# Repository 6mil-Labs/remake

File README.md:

# REMAKE

REMAKE is a **36-key wireless split keyboard** designed by **Felipe Balbi**
around RMK firmware. Its name includes **RMK**.

Each half has 15 finger keys and a three-key thumb cluster. The stepped board
outline follows the column stagger and thumb fan. Both halves use the same
reversible PCB: manufacture **two separate, identical boards** and populate
them in opposite orientations. No panelization or mouse bites are required.

## Revision validation status

| Revision | Status |
|---|---|
| REV 0.1 | Fully validated |
| REV 0.2 | Fully validated |
| [REV 0.3](https://github.com/6mil-Labs/remake/releases/tag/v0.3) | Current prerelease; physical validation remains required |

> **REV 0.3 is prototype hardware, not production-fit or safety certification.** The current design has
> **18 keys per half / 36 total.** Routing is complete, ground pours are filled,
> and the outline is closed with straight runs and circular fillets, with at least
> **3.5 mm nominal switch-body margin** around the key matrix. SW17's
> larger PCB envelope contains a **26.5×16.5 mm cap**, rotated
> 90° relative to its original thumb fan; other caps use **17.5×16.5 mm** envelopes.
> The minimum nominal thumb-to-row gap is approximately **0.660 mm**.
> Production tolerances and moving-key fit have not been physically validated.
> Component selection and physical validation are incomplete. The battery
> receptacles moved **4 mm upward** to improve lead reach. **PCB v0.3 uses
> Case v1.0**, not Case v0.2. Firmware is maintained and tested separately.

## v0.3 release and editable sources

- [Published v0.3 prerelease](https://github.com/6mil-Labs/remake/releases/tag/v0.3):
  fabrication ZIP, schematic PDF, assembly PNG/STEP previews, Case v1.0 left/right
  STEP bodies, model-coverage notes, and `SHA256SUMS`.
- [Tagged v0.3 sources](https://github.com/6mil-Labs/remake/tree/v0.3): editable
  KiCad project/schematic/PCB and FreeCAD case sources. GitHub's source archives
  on the release page contain these files; Gerbers and STEP exports are not a
  replacement for the editable sources.

Use two identical PCBs per keyboard. Keep assembly models (`remake-*.step`)
separate from case bodies (`case-v1.0-*.step`), and review model omissions and
physical-fit requirements before fabrication or assembly.

## Repository layout

| Path | Contents |
|---|---|
| [`hw/`](hw/) | KiCad project, schematic, PCB, local libraries and library tables |
| [`cad/`](cad/) | Component models, source manifest and third-party notices |
| [`docs/`](docs/) | Assembly, manufacturing and component references |
| [`docs/assets/`](docs/assets/) | Vector logo and source artwork |
| [`.github/workflows/`](.github/workflows/) | KiCad checks; no automatic source commits |

The root contains project-level documentation and licensing. Generated reports
and exports belong in ignored output directories, not alongside source files.

## Open the hardware

Use **KiCad 10.0.7 or newer** and open [`hw/remake.kicad_pro`](hw/remake.kicad_pro).
Local library tables and project-relative model paths travel with the project.

On this machine, use the following workaround for the native Wayland issue:

```sh
GDK_BACKEND=x11 kicad hw/remake.kicad_pro
```

Read [assembly](docs/assembly.md) before building. The
[component reference](docs/components.md) records sources, licences and model
limitations; a rendering is not proof of fit. The regression suite checks
schematic-to-PCB associations separately from electrical parity.

## Firmware

[REMAKE Miryoku](https://github.com/6mil-Labs/remake-miryoku) contains the
RMK-based firmware, complete keyboard configuration, build/flash instructions,
and native tests. It provides left/central and right/peripheral UF2 images;
flash matching builds to both nice!nano v2 controllers. Firmware is versioned
separately from the PCB: use its documented REMAKE pin mapping and check the
actual assembly. Hardware CI does not build or certify the firmware.

## Checks

Run from the repository root, with reports outside the source tree:

```sh
mkdir -p .remake-checks
kicad-cli pcb drc --format json --refill-zones --schematic-parity \
  --output .remake-checks/drc.json hw/remake.kicad_pcb
kicad-cli sch erc --format json \
  --output .remake-checks/erc.json hw/remake.kicad_sch
```

Before fabrication, require clean refilled DRC, zero unconnected items and
schematic parity, and review all ERC findings. Use `--exit-code-violations` for
gated checks. Do not hide findings, weaken rules or bridge selection jumpers
to make checks pass. Component-rating, physical assembly, battery-safety and
prototype/RF checks remain required even when CAD checks pass.

Run the regression suite as well:

```sh
python3 -m unittest discover -s tests -v
```

## Draft releases

Pushing a tag runs the same required CI on that exact commit. Only after CI
and fabrication packaging succeed does the workflow create a **draft** GitHub
Release containing one-design JLCPCB fabrication ZIP, a schematic PDF,
left/right PNG and STEP previews, compatible Case v1.0 body STEP files,
model-coverage notes and checksums. These files are separate attachments, never
additional designs inside the JLCPCB ZIP. The STEP assemblies are partial;
check their coverage notes before case design. Branch/PR CI also exports the
case solids for both case versions as the `case-steps` artifact, including on
case-only changes. PCB v0.3 uses Case v1.0; case and PCB revision numbers differ.
Review and publish the draft manually; failed, cancelled or skipped prerequisites
block release creation. Passing CI is not physical/fabrication approval.

See [manufacturing and release details](docs/manufacturing.md) for archive
contents, validation limits and retry behavior.

## OSHWA certification

REMAKE is **not yet OSHWA-certified**. Open-source licensing, passing CI, and
the generic open-hardware gear logo are not the OSHWA certification mark.

The [submission guide](docs/oshwa.md) documents the standard-library Python
helper, API-token signup, and editable application template. Preview is offline
by default; submitting requires explicit legal declarations and `--submit`.
Point an application at the public source/release version being certified, not
an unpublished future v1.0. Wait for OSHWA approval and a UID before using the
certification mark on a PCB.

## Contributing and licensing

See [CONTRIBUTING.md](CONTRIBUTING.md) for source organization and validation
expectations.

**Copyright © 2026 Felipe Balbi.** REMAKE is licensed under the
**CERN Open Hardware Licence Version 2 — Strongly Reciprocal**
([CERN-OHL-S-2.0](LICENSE)); see [COPYRIGHT](COPYRIGHT) for the project notice.
Project-authored written documentation and original documentation illustrations
are additionally available under [CC-BY-SA-4.0](LICENSE-DOCUMENTATION.md), at
your option. Hardware/design files retain their existing licence.
Imported third-party component models and library sources retain their
documented licences and notices. Local-only models with unresolved
redistribution rights are not covered by the project licence grant.

### Manufacturing and sales

Interested in manufacturing or selling REMAKE boards or kits? I'd love to hear
from you! Please [open a manufacturing and sales issue](https://github.com/6mil-Labs/remake/issues/new?template=manufacturing-and-sales.yml)
to discuss revisions, manufacturing feedback, and opportunities to collaborate.
You can also opt in to a future seller list to help people find bare PCBs, kits,
or assembled keyboards without building everything themselves.

Commercial manufacture and sale are permitted under [CERN-OHL-S-2.0](LICENSE),
subject to its requirements. Contacting the maintainer is encouraged, but is not
a condition of exercising those rights. Third-party products must not be
presented as officially endorsed without permission.

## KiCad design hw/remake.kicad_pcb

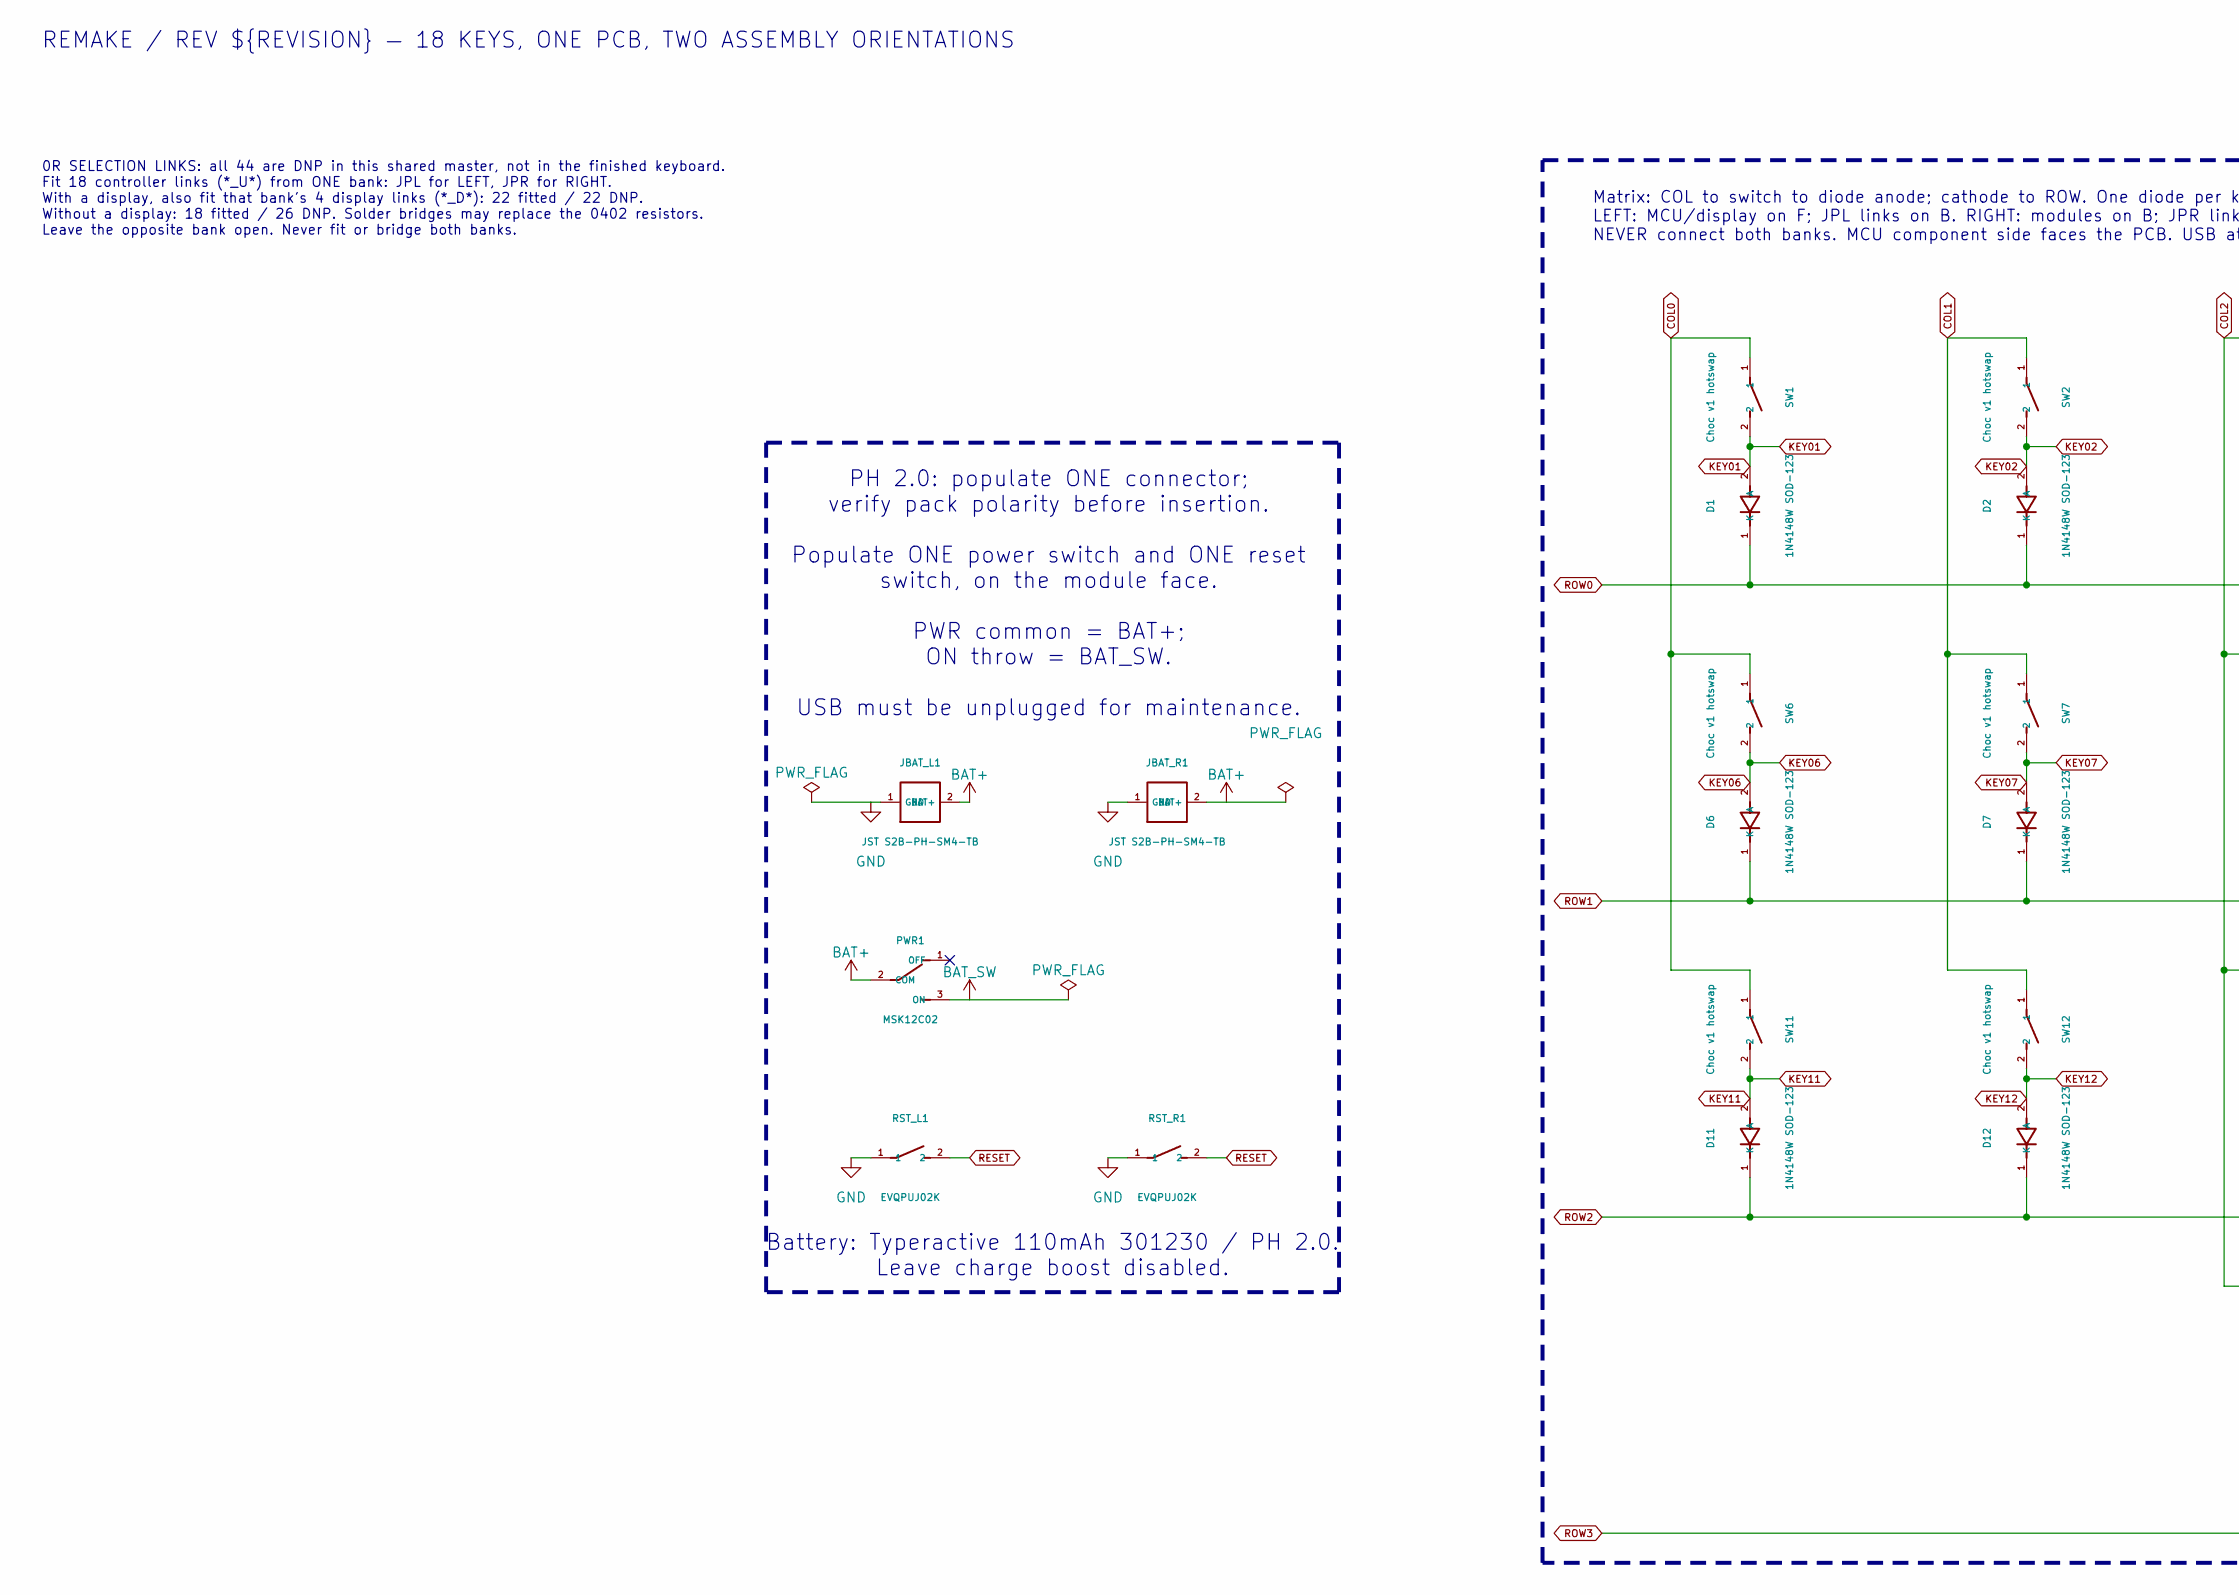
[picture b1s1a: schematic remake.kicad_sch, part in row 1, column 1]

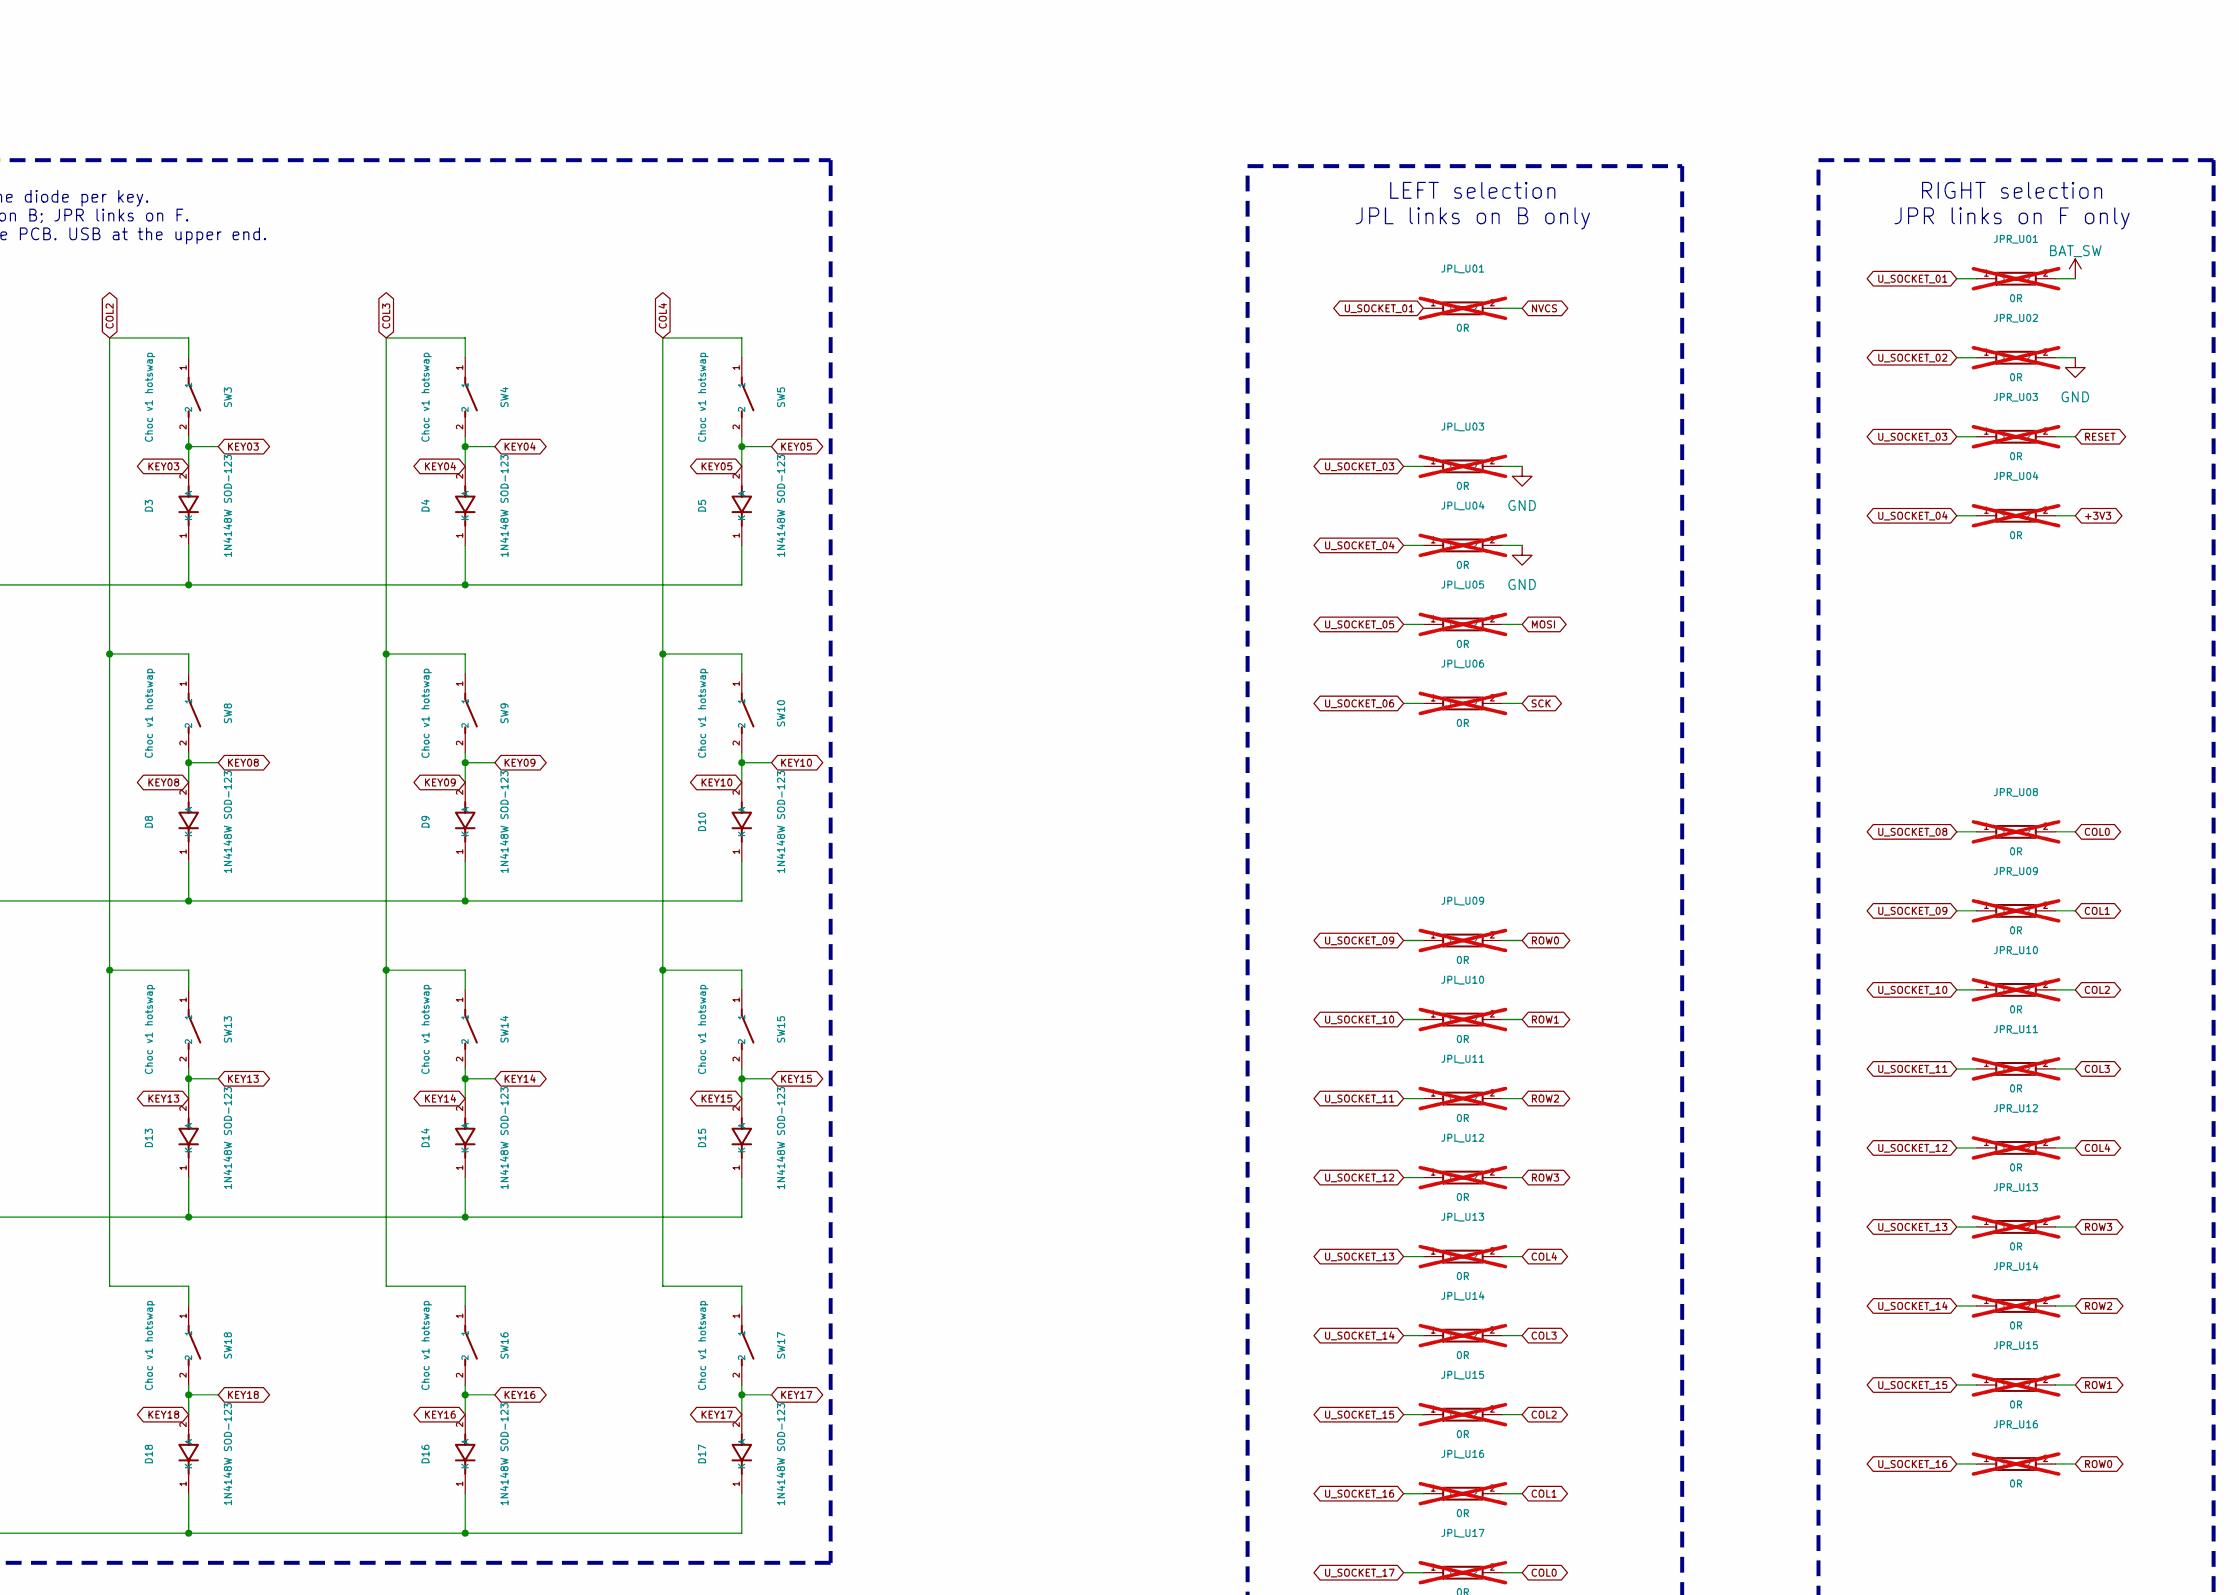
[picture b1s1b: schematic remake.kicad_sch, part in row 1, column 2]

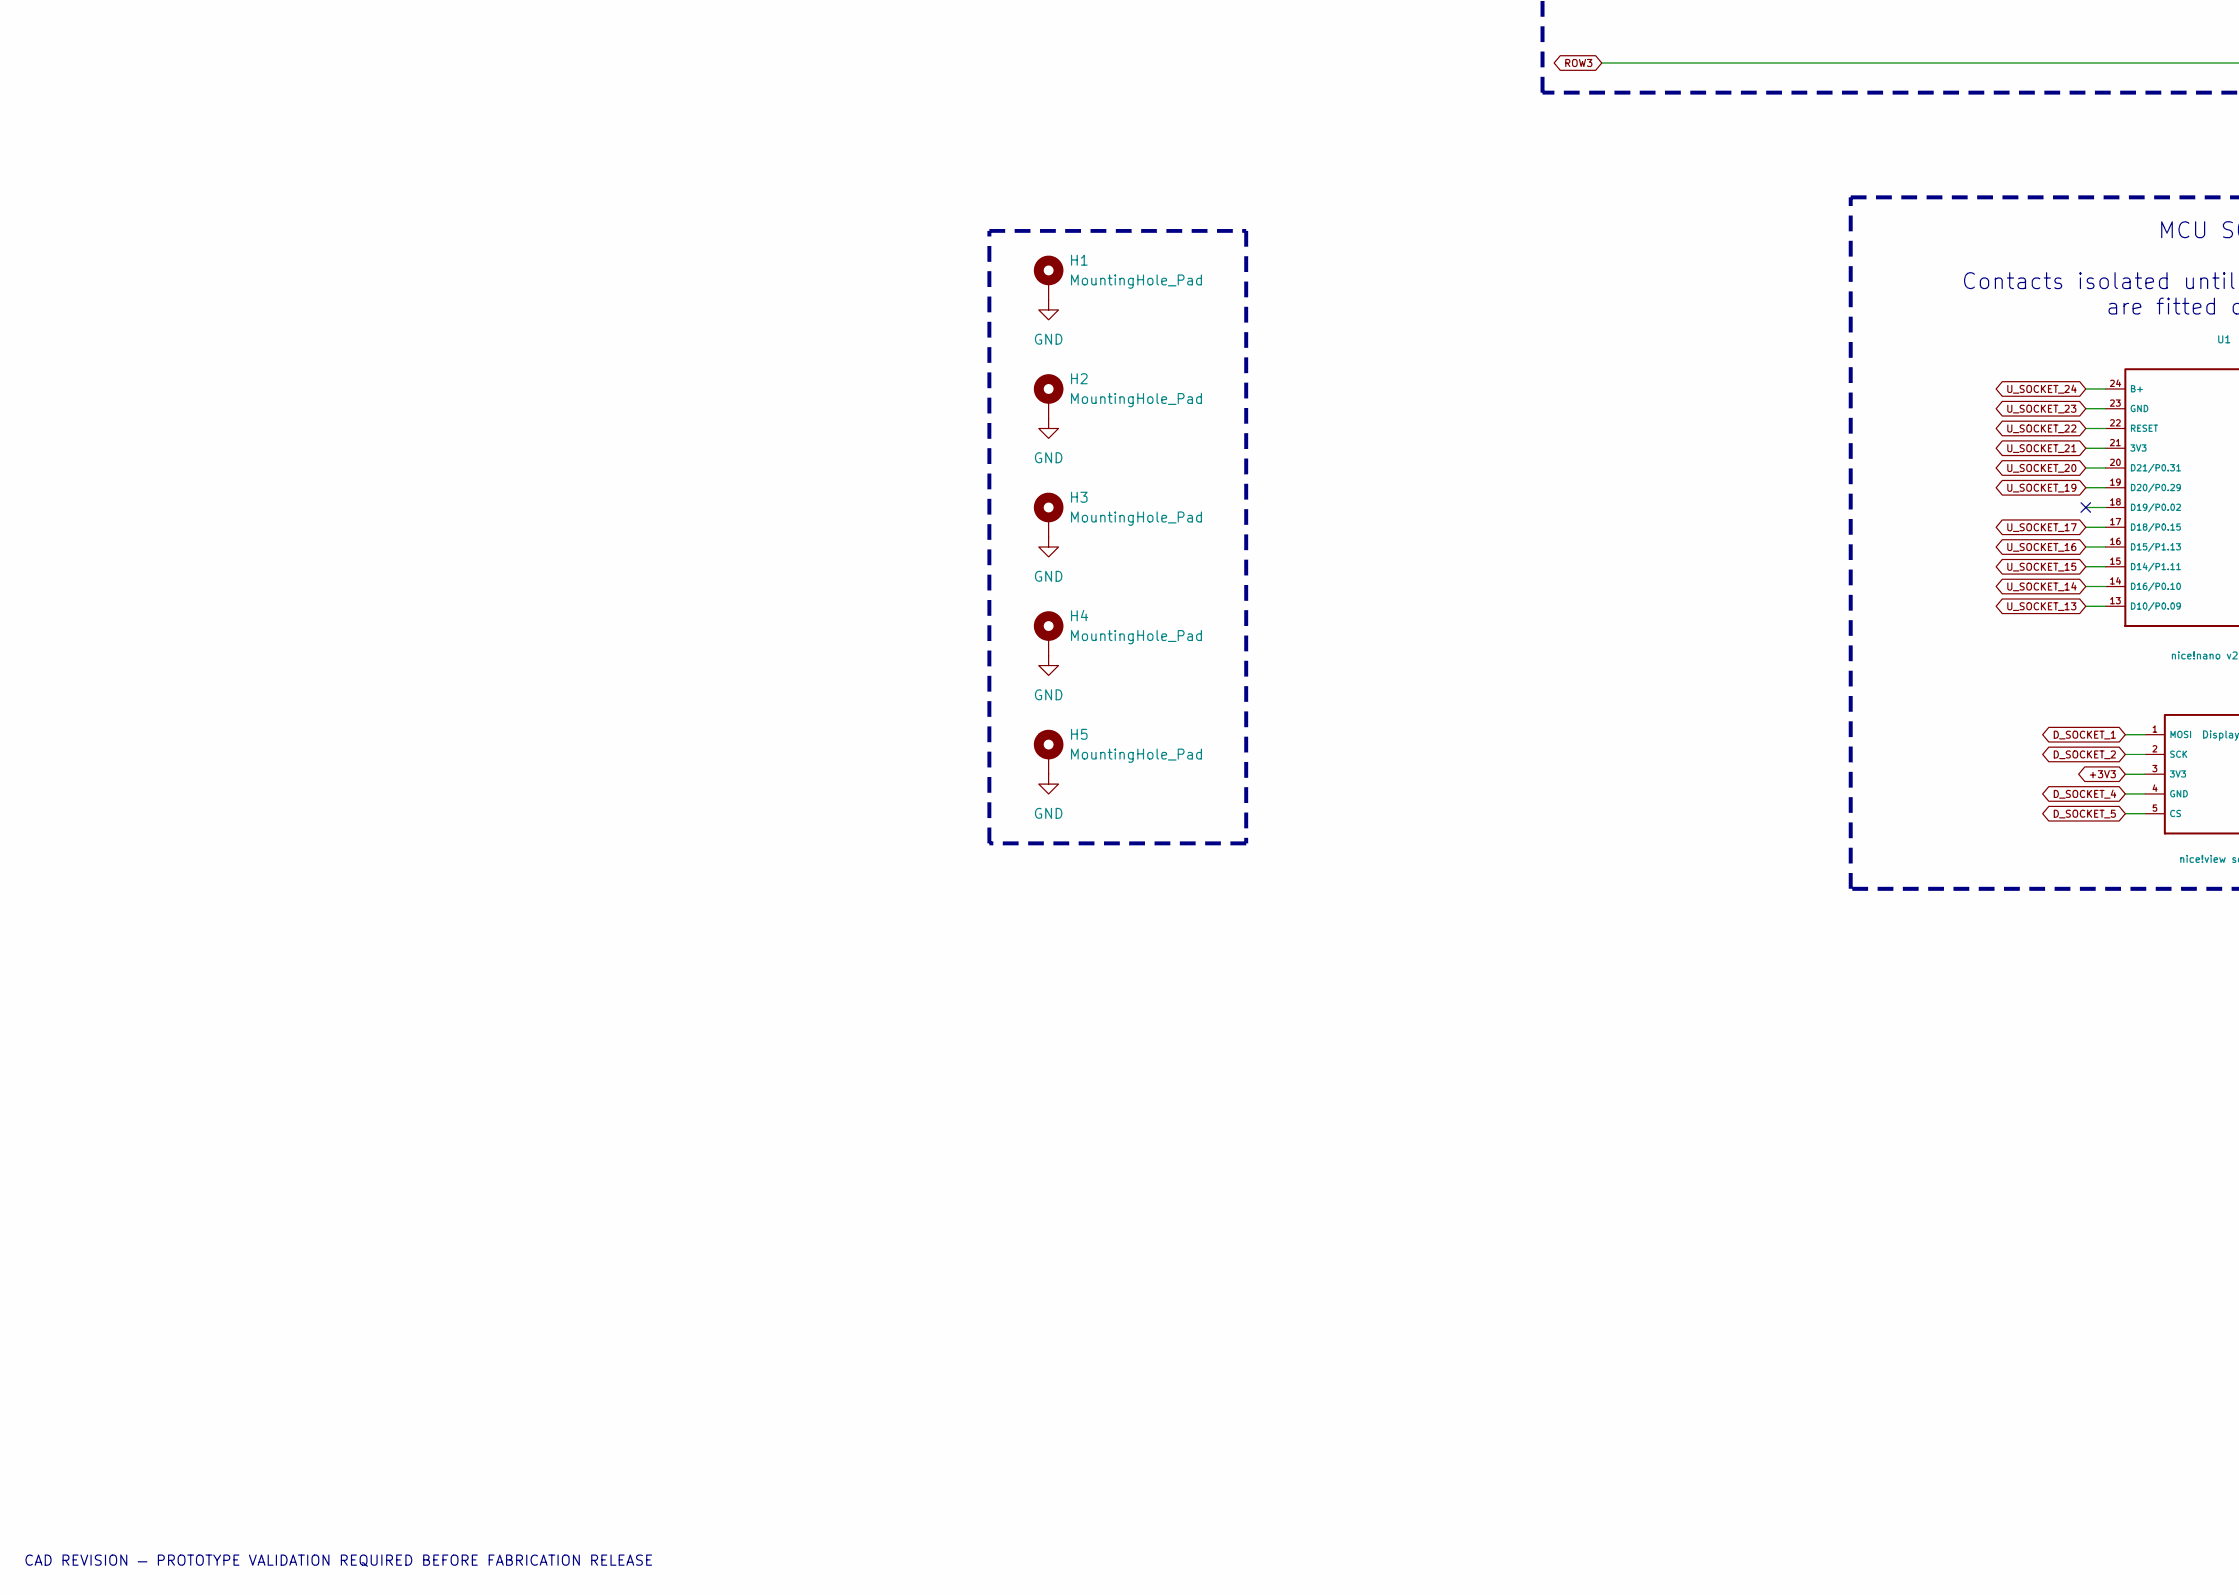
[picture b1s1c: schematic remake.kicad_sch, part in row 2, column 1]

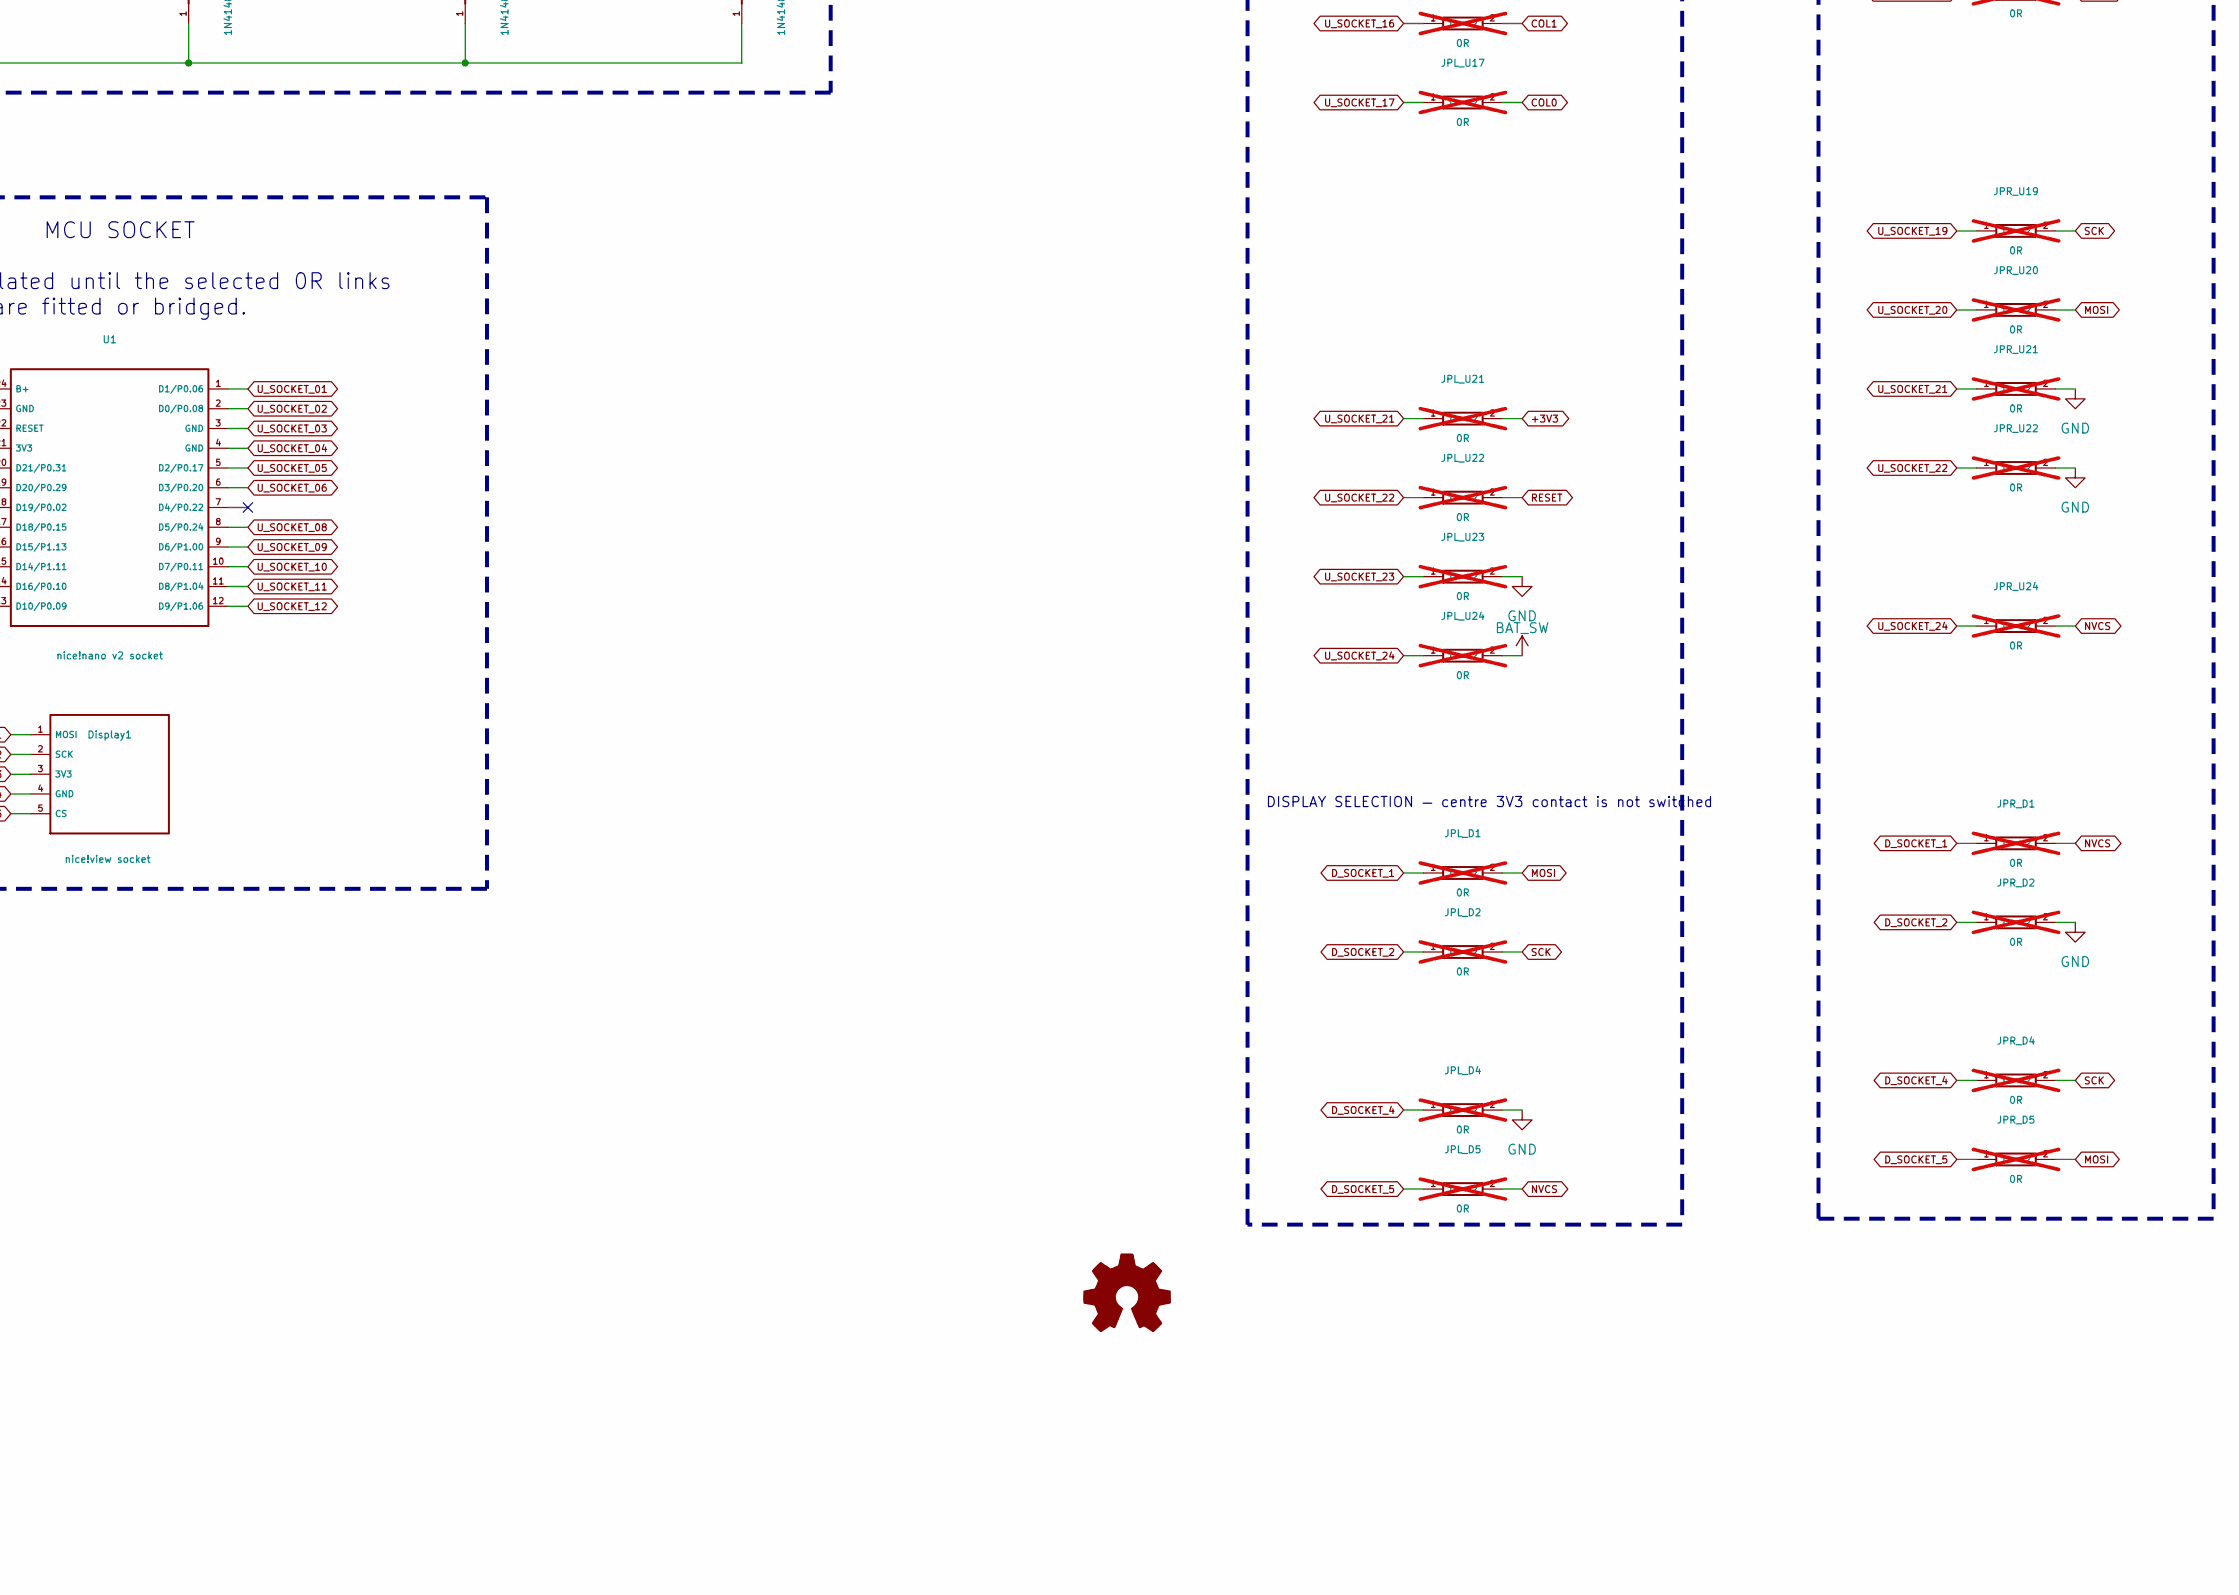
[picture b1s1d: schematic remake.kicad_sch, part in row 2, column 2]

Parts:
D1, D2, D3, D4, D5, D6, D7, D8, D9, D10, D11, D12, D13, D14, D15, D16, D17, D18: 1N4148W SOD-123; Diode_SOD123_reversible
Display1: nice!view socket; nice_view_reversible
H1, H2, H3, H4, H5: MountingHole_Pad; MountingHole_2.2mm_M2_ISO7380_Pad_TopBottom
JBAT_L1: JST S2B-PH-SM4-TB; JST_PH_2mm_side_entry
JBAT_R1: JST S2B-PH-SM4-TB; JST_PH_2mm_side_entry
JPL_D1, JPL_D2, JPL_D4, JPL_D5: 0R; R_0402_1005Metric_SolderJumper; not fitted
JPL_U01, JPL_U03, JPL_U04, JPL_U05, JPL_U06, JPL_U09, JPL_U10, JPL_U11, JPL_U12, JPL_U13, JPL_U14, JPL_U15, JPL_U16, JPL_U17, JPL_U21, JPL_U22, JPL_U23, JPL_U24: 0R; R_0402_1005Metric_SolderJumper; not fitted
JPR_D1, JPR_D2, JPR_D4, JPR_D5: 0R; R_0402_1005Metric_SolderJumper; not fitted
JPR_U01, JPR_U02, JPR_U03, JPR_U04, JPR_U08, JPR_U09, JPR_U10, JPR_U11, JPR_U12, JPR_U13, JPR_U14, JPR_U15, JPR_U16, JPR_U19, JPR_U20, JPR_U21, JPR_U22, JPR_U24: 0R; R_0402_1005Metric_SolderJumper; not fitted
PWR1: MSK12C02; SW_Power_MSK12C02_reversible
RST_L1: EVQPUJ02K; SW_SPST_Panasonic_EVQPUJ02K
RST_R1: EVQPUJ02K; SW_SPST_Panasonic_EVQPUJ02K
SW1, SW2, SW3, SW4, SW5, SW6, SW7, SW8, SW9, SW10, SW11, SW12, SW13, SW14, SW15, SW16, SW17, SW18: Choc v1 hotswap; SW_Hotswap_Kailh_Choc_V1_reversible
U1: nice!nano v2 socket; nice_nano_reversible

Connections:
+3V3: Display1.3 (3V3), JPL_U21.2, JPR_U04.2
BAT+: JBAT_L1.2 (BAT+), JBAT_R1.2 (BAT+), PWR1.2 (COM)
BAT_SW: JPL_U24.2, JPR_U01.2, PWR1.3 (ON)
COL0: JPL_U17.2, JPR_U08.2, SW1.1, SW6.1, SW11.1
COL1: JPL_U16.2, JPR_U09.2, SW2.1, SW7.1, SW12.1
COL2: JPL_U15.2, JPR_U10.2, SW3.1, SW8.1, SW13.1, SW18.1
COL3: JPL_U14.2, JPR_U11.2, SW4.1, SW9.1, SW14.1, SW16.1
COL4: JPL_U13.2, JPR_U12.2, SW5.1, SW10.1, SW15.1, SW17.1
D_SOCKET_1: Display1.1 (MOSI), JPL_D1.1, JPR_D1.1
D_SOCKET_2: Display1.2 (SCK), JPL_D2.1, JPR_D2.1
D_SOCKET_4: Display1.4 (GND), JPL_D4.1, JPR_D4.1
D_SOCKET_5: Display1.5 (CS), JPL_D5.1, JPR_D5.1
GND: H1.1 (1_1), H2.1 (1_1), H3.1 (1_1), H4.1 (1_1), H5.1 (1_1), JBAT_L1.1 (GND), JBAT_R1.1 (GND), JPL_D4.2, JPL_U03.2, JPL_U04.2, JPL_U23.2, JPR_D2.2, JPR_U02.2, JPR_U21.2, JPR_U22.2, RST_L1.1, RST_R1.1
KEY01: D1.2 (A), SW1.2
KEY02: D2.2 (A), SW2.2
KEY03: D3.2 (A), SW3.2
KEY04: D4.2 (A), SW4.2
KEY05: D5.2 (A), SW5.2
KEY06: D6.2 (A), SW6.2
KEY07: D7.2 (A), SW7.2
KEY08: D8.2 (A), SW8.2
KEY09: D9.2 (A), SW9.2
KEY10: D10.2 (A), SW10.2
KEY11: D11.2 (A), SW11.2
KEY12: D12.2 (A), SW12.2
KEY13: D13.2 (A), SW13.2
KEY14: D14.2 (A), SW14.2
KEY15: D15.2 (A), SW15.2
KEY16: D16.2 (A), SW16.2
KEY17: D17.2 (A), SW17.2
KEY18: D18.2 (A), SW18.2
MOSI: JPL_D1.2, JPL_U05.2, JPR_D5.2, JPR_U20.2
NVCS: JPL_D5.2, JPL_U01.2, JPR_D1.2, JPR_U24.2
RESET: JPL_U22.2, JPR_U03.2, RST_L1.2, RST_R1.2
ROW0: D1.1 (K), D2.1 (K), D3.1 (K), D4.1 (K), D5.1 (K), JPL_U09.2, JPR_U16.2
ROW1: D6.1 (K), D7.1 (K), D8.1 (K), D9.1 (K), D10.1 (K), JPL_U10.2, JPR_U15.2
ROW2: D11.1 (K), D12.1 (K), D13.1 (K), D14.1 (K), D15.1 (K), JPL_U11.2, JPR_U14.2
ROW3: D16.1 (K), D17.1 (K), D18.1 (K), JPL_U12.2, JPR_U13.2
SCK: JPL_D2.2, JPL_U06.2, JPR_D4.2, JPR_U19.2
U_SOCKET_01: JPL_U01.1, JPR_U01.1, U1.1 (D1/P0.06)
U_SOCKET_02: JPR_U02.1, U1.2 (D0/P0.08)
U_SOCKET_03: JPL_U03.1, JPR_U03.1, U1.3 (GND)
U_SOCKET_04: JPL_U04.1, JPR_U04.1, U1.4 (GND)
U_SOCKET_05: JPL_U05.1, U1.5 (D2/P0.17)
U_SOCKET_06: JPL_U06.1, U1.6 (D3/P0.20)
U_SOCKET_08: JPR_U08.1, U1.8 (D5/P0.24)
U_SOCKET_09: JPL_U09.1, JPR_U09.1, U1.9 (D6/P1.00)
U_SOCKET_10: JPL_U10.1, JPR_U10.1, U1.10 (D7/P0.11)
U_SOCKET_11: JPL_U11.1, JPR_U11.1, U1.11 (D8/P1.04)
U_SOCKET_12: JPL_U12.1, JPR_U12.1, U1.12 (D9/P1.06)
U_SOCKET_13: JPL_U13.1, JPR_U13.1, U1.13 (D10/P0.09)
U_SOCKET_14: JPL_U14.1, JPR_U14.1, U1.14 (D16/P0.10)
U_SOCKET_15: JPL_U15.1, JPR_U15.1, U1.15 (D14/P1.11)
U_SOCKET_16: JPL_U16.1, JPR_U16.1, U1.16 (D15/P1.13)
U_SOCKET_17: JPL_U17.1, U1.17 (D18/P0.15)
U_SOCKET_19: JPR_U19.1, U1.19 (D20/P0.29)
U_SOCKET_20: JPR_U20.1, U1.20 (D21/P0.31)
U_SOCKET_21: JPL_U21.1, JPR_U21.1, U1.21 (3V3)
U_SOCKET_22: JPL_U22.1, JPR_U22.1, U1.22 (RESET)
U_SOCKET_23: JPL_U23.1, U1.23 (GND)
U_SOCKET_24: JPL_U24.1, JPR_U24.1, U1.24 (B+)

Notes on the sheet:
DISPLAY SELECTION — centre 3V3 contact is not switched
CAD REVISION — PROTOTYPE VALIDATION REQUIRED BEFORE FABRICATION RELEASE
REMAKE / REV ${REVISION} — 18 KEYS, ONE PCB, TWO ASSEMBLY ORIENTATIONS
LEFT selection JPL links on B only
PH 2.0: populate ONE connector; verify pack polarity before insertion. Populate ONE power switch and ONE reset switch, on the module face. PWR common = BAT+; ON throw = BAT_SW. USB must be unplugged for maintenance.
MCU SOCKET Contacts isolated until the selected 0R links are fitted or bridged.
Matrix: COL to switch to diode anode; cathode to ROW. One diode per key. LEFT: MCU/display on F; JPL links on B. RIGHT: modules on B; JPR links on F. NEVER connect both banks. MCU component side faces the PCB. USB at the upper end.
Battery: Typeractive 110mAh 301230 / PH 2.0. Leave charge boost disabled.
RIGHT selection JPR links on F only
0R SELECTION LINKS: all 44 are DNP in this shared master, not in the finished keyboard. Fit 18 controller links (*_U*) from ONE bank: JPL for LEFT, JPR for RIGHT. With a display, also fit that bank's 4 display links (*_D*): 22 fitted / 22 DNP. Without a display: 18 fitted / 26 DNP. Solder bridges m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

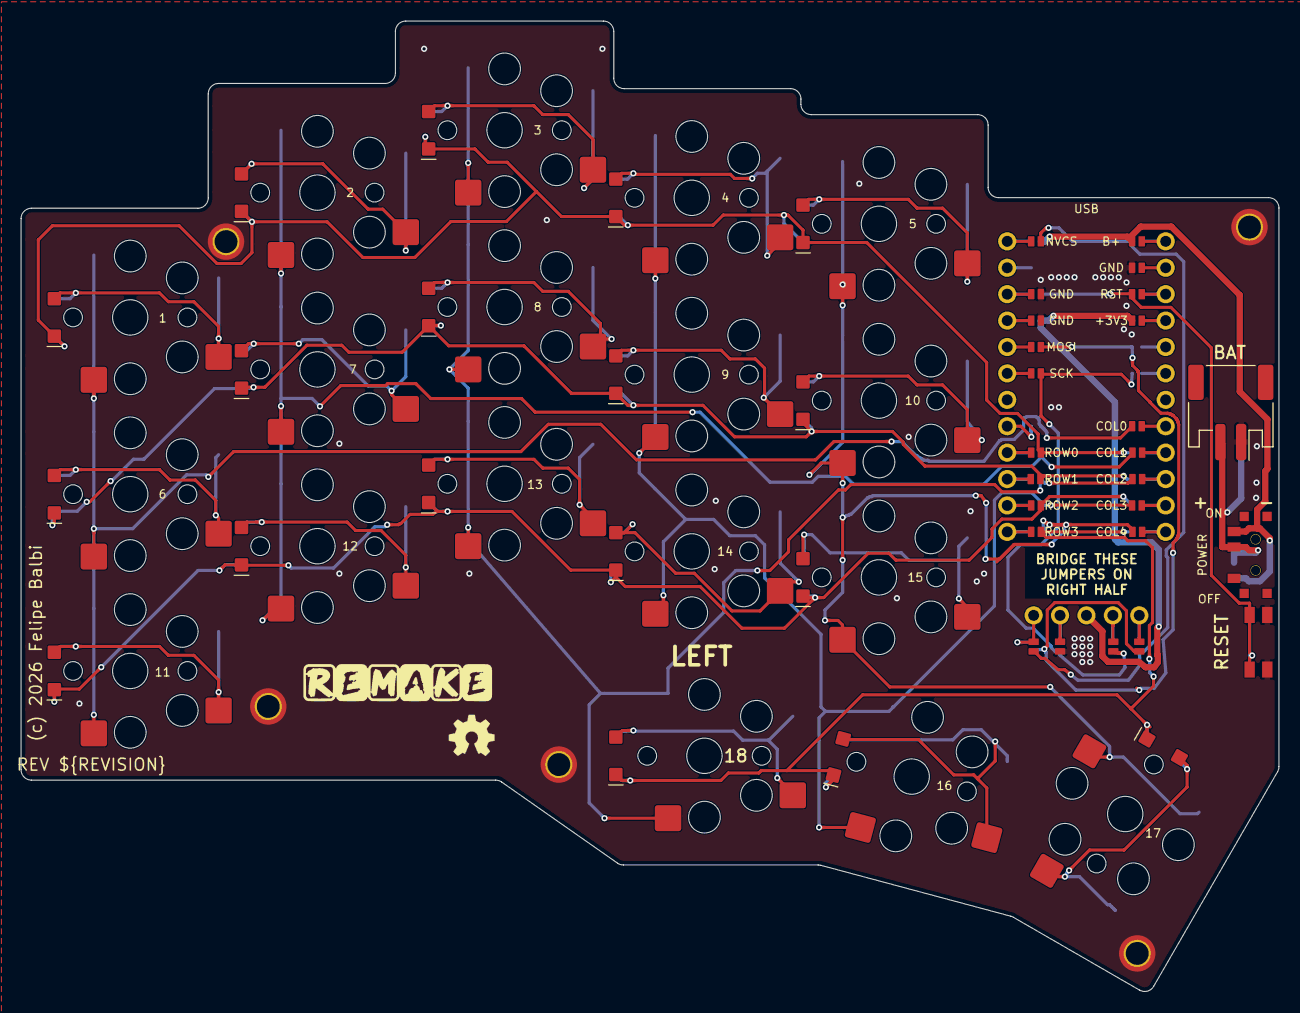
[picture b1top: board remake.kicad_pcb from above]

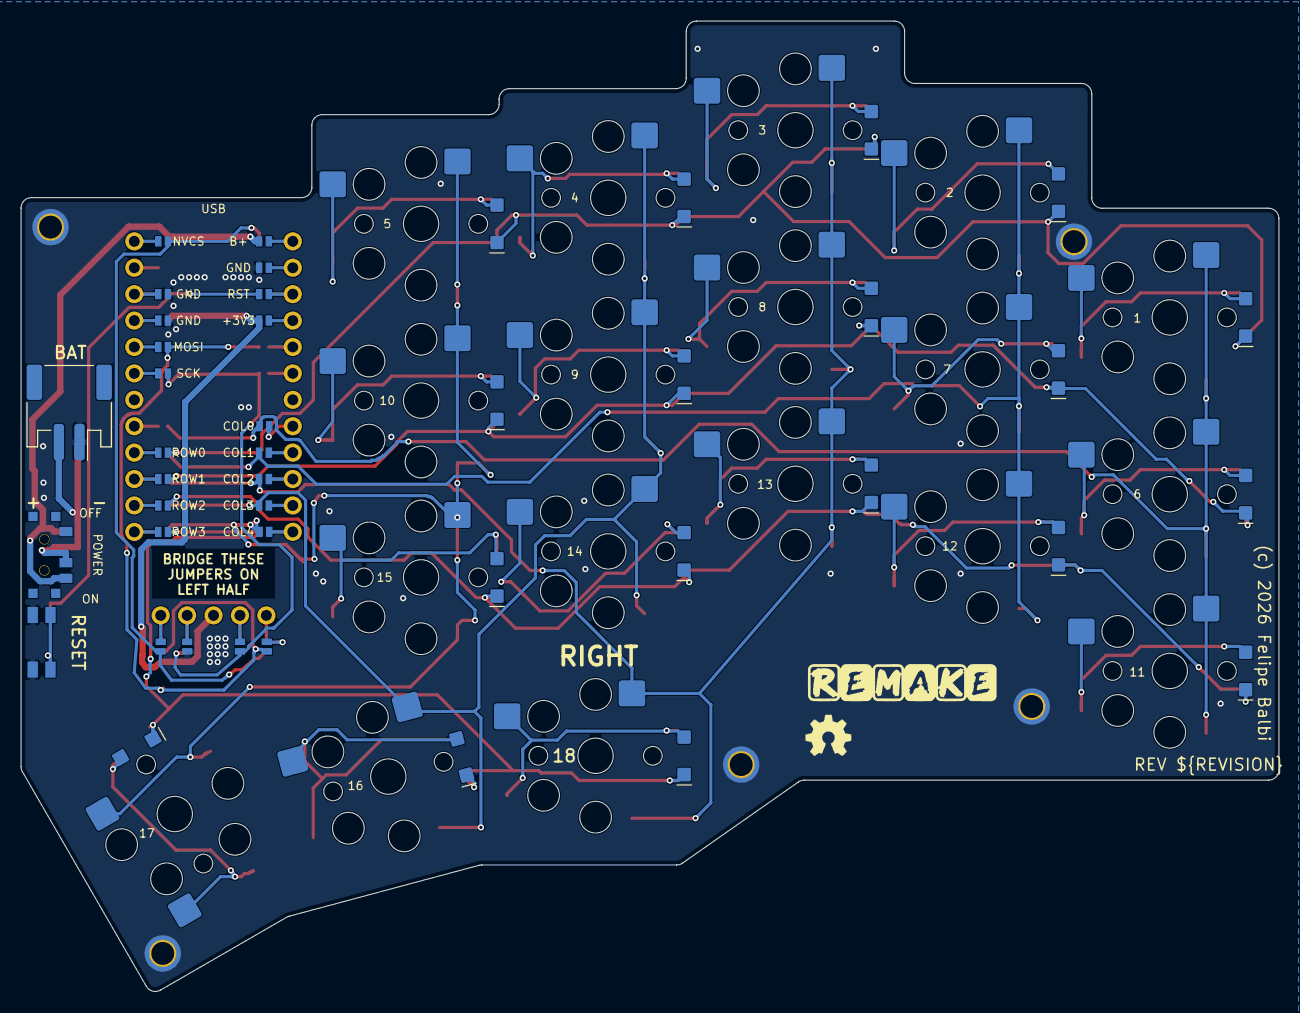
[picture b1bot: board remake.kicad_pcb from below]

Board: 2 copper layers, 121.0 x 93.3 mm, 95 parts (25 on the bottom side), 61 nets.

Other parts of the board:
LOGO1: REMAKE; Logo_REMAKE
LOGO2, LOGO3: OSHW_Gear_4mm

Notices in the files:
hw/remake.kicad_pcb:
(c) 2026 Felipe Balbi
